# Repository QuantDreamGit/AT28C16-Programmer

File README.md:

# 🧠 8-bit EEPROM Programmer & Display Decoder

This project implements an EEPROM-based lookup table to convert an 8-bit value into decimal digits using a hardware-only decoding approach.

The EEPROM is programmed using an Arduino Nano Every and a shift-register-driven address bus.

## 📌 Overview

The system:

* Converts `0x00–0xFF` into decimal digits
* Supports both **unsigned** and **two’s complement signed** formats
* Uses EEPROM as a **hardware lookup table**
* Drives a segmented display via precomputed values

## ⚙️ Architecture

* **MCU**: Arduino Nano Every (20 MHz)
* **Shift Register**: 74HC164 (serial → parallel address)
* **EEPROM**: AT28Cxx family
* **Data bus**: 8-bit parallel
* **Control signals**: `WE`, `OE`, `CLR`

Addresses are shifted serially into the 74HC164, while data is written in parallel.

## 🧩 EEPROM Memory Map

### Unsigned (`0x00–0xFF`)

| Address       | Content       |
| ------------- | ------------- |
| `0x000–0x0FF` | Ones          |
| `0x100–0x1FF` | Tens          |
| `0x200–0x2FF` | Hundreds      |
| `0x300–0x3FF` | Sign (`0x00`) |

### Signed (`-128 → 127`)

| Address       | Content                |
| ------------- | ---------------------- |
| `0x400–0x4FF` | Ones                   |
| `0x500–0x5FF` | Tens                   |
| `0x600–0x6FF` | Hundreds               |
| `0x700–0x7FF` | Sign (`0x00` / `0x80`) |

* Digits use `abs(value)`
* Negative numbers use sign byte `0x80`

## 🔢 Segment Encoding

| Digit | Hex    |
| ----- | ------ |
| 0     | `0x7B` |
| 1     | `0x12` |
| 2     | `0xB9` |
| 3     | `0xB3` |
| 4     | `0xD2` |
| 5     | `0xE3` |
| 6     | `0xEB` |
| 7     | `0x32` |
| 8     | `0xFB` |
| 9     | `0xF2` |
| -     | `0x80` |

## 🛠️ Programming Flow

For each byte:

1. Clear shift register
2. Shift 11-bit address (MSB → LSB)
3. Set data bus (`D0–D7`)
4. Pulse `WE` (write enable)
5. Wait for write cycle (~2 ms)

Readback uses the same address logic with `OE` enabled.

## ⚡ Timing Notes

* Arduino @ 20 MHz → ~50 ns per cycle
* `digitalWrite()` already satisfies all timing constraints
* EEPROM write cycle dominates (~1–2 ms)
* No latch in 74HC164 → register is cleared before each address load

## 🖼️ Assets

### Schematic

### PCB

### 3D View

### Gerbers

---

## 📁 Structure

```plaintext
.
├── firmware/
├── hardware/
├── images/
└── README.md
```

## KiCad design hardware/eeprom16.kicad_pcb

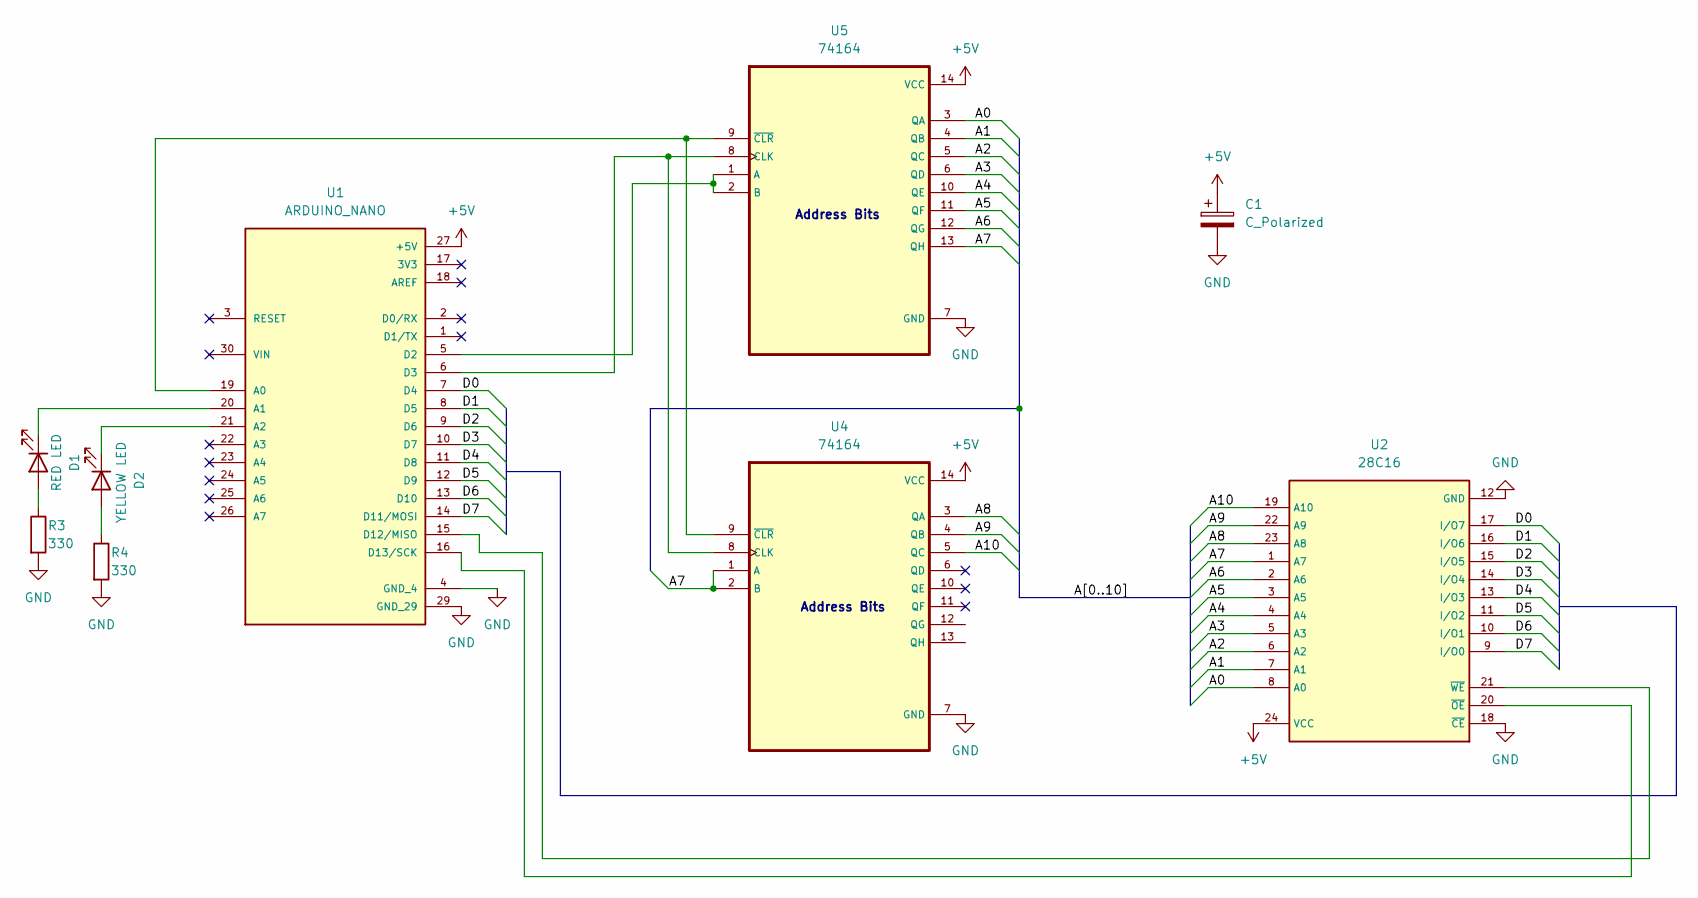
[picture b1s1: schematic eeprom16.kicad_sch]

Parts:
C1: C_Polarized; CP_Radial_D10.0mm_P3.50mm
D1: RED LED; LED_D4.0mm
D2: YELLOW LED; LED_D4.0mm
R3, R4: 330; R_Axial_DIN0204_L3.6mm_D1.6mm_P5.08mm_Horizontal
U1: ARDUINO_NANO; Arduino_Nano; PARTREV 30/06/2021
U2: 28C16; DIP-24_W15.24mm_Socket
U4, U5: 74164; DIP-14_W7.62mm_Socket

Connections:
+5V: C1.1, U1.27 (+5V), U2.24 (VCC), U4.14 (VCC), U5.14 (VCC)
/A0: U2.8 (A0), U5.3 (QA)
/A1: U2.7 (A1), U5.4 (QB)
/A2: U2.6 (A2), U5.5 (QC)
/A3: U2.5 (A3), U5.6 (QD)
/A4: U2.4 (A4), U5.10 (QE)
/A5: U2.3 (A5), U5.11 (QF)
/A6: U2.2 (A6), U5.12 (QG)
/A7: U2.1 (A7), U4.1 (A), U4.2 (B), U5.13 (QH)
/A8: U2.23 (A8), U4.3 (QA)
/A9: U2.22 (A9), U4.4 (QB)
/A10: U2.19 (A10), U4.5 (QC)
/D0: U1.7 (D4), U2.17 (I/O7)
/D1: U1.8 (D5), U2.16 (I/O6)
/D2: U1.9 (D6), U2.15 (I/O5)
/D3: U1.10 (D7), U2.14 (I/O4)
/D4: U1.11 (D8), U2.13 (I/O3)
/D5: U1.12 (D9), U2.11 (I/O2)
/D6: U1.13 (D10), U2.10 (I/O1)
/D7: U1.14 (D11/MOSI), U2.9 (I/O0)
GND: C1.2, R3.2, R4.2, U1.4 (GND_4), U1.29 (GND_29), U2.12 (GND), U2.18 (~CE), U4.7 (GND), U5.7 (GND)
unnamed: D1.2 (A), R3.1
unnamed: D1.1 (K), U1.20 (A1)
unnamed: D2.2 (A), R4.1
unnamed: D2.1 (K), U1.21 (A2)
unnamed: U1.19 (A0), U4.9 (~CLR), U5.9 (~CLR)
unnamed: U1.5 (D2), U5.1 (A), U5.2 (B)
unnamed: U1.6 (D3), U4.8 (CLK), U5.8 (CLK)
unnamed: U1.15 (D12/MISO), U2.21 (~WE)
unnamed: U1.16 (D13/SCK), U2.20 (~OE)

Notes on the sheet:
Address Bits

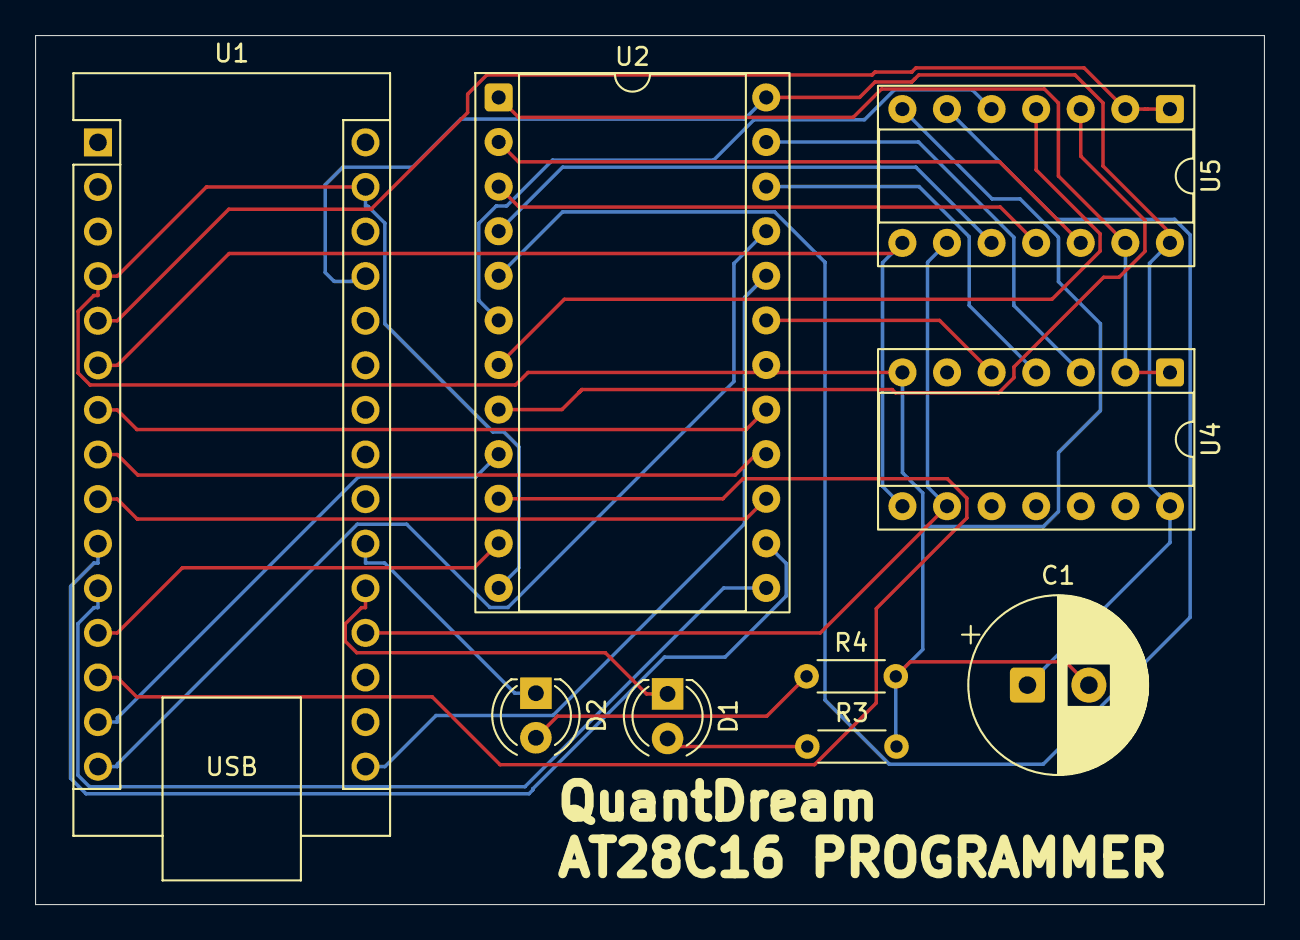
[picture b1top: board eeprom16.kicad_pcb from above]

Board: 2 copper layers, 70.0 x 49.5 mm, 9 parts (0 on the bottom side), 30 nets.

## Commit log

2026-04-08 Revise README with project details and structure
    Updated project description and added detailed sections on architecture, EEPROM memory map, segment encoding, programming flow, timing notes, and assets.
